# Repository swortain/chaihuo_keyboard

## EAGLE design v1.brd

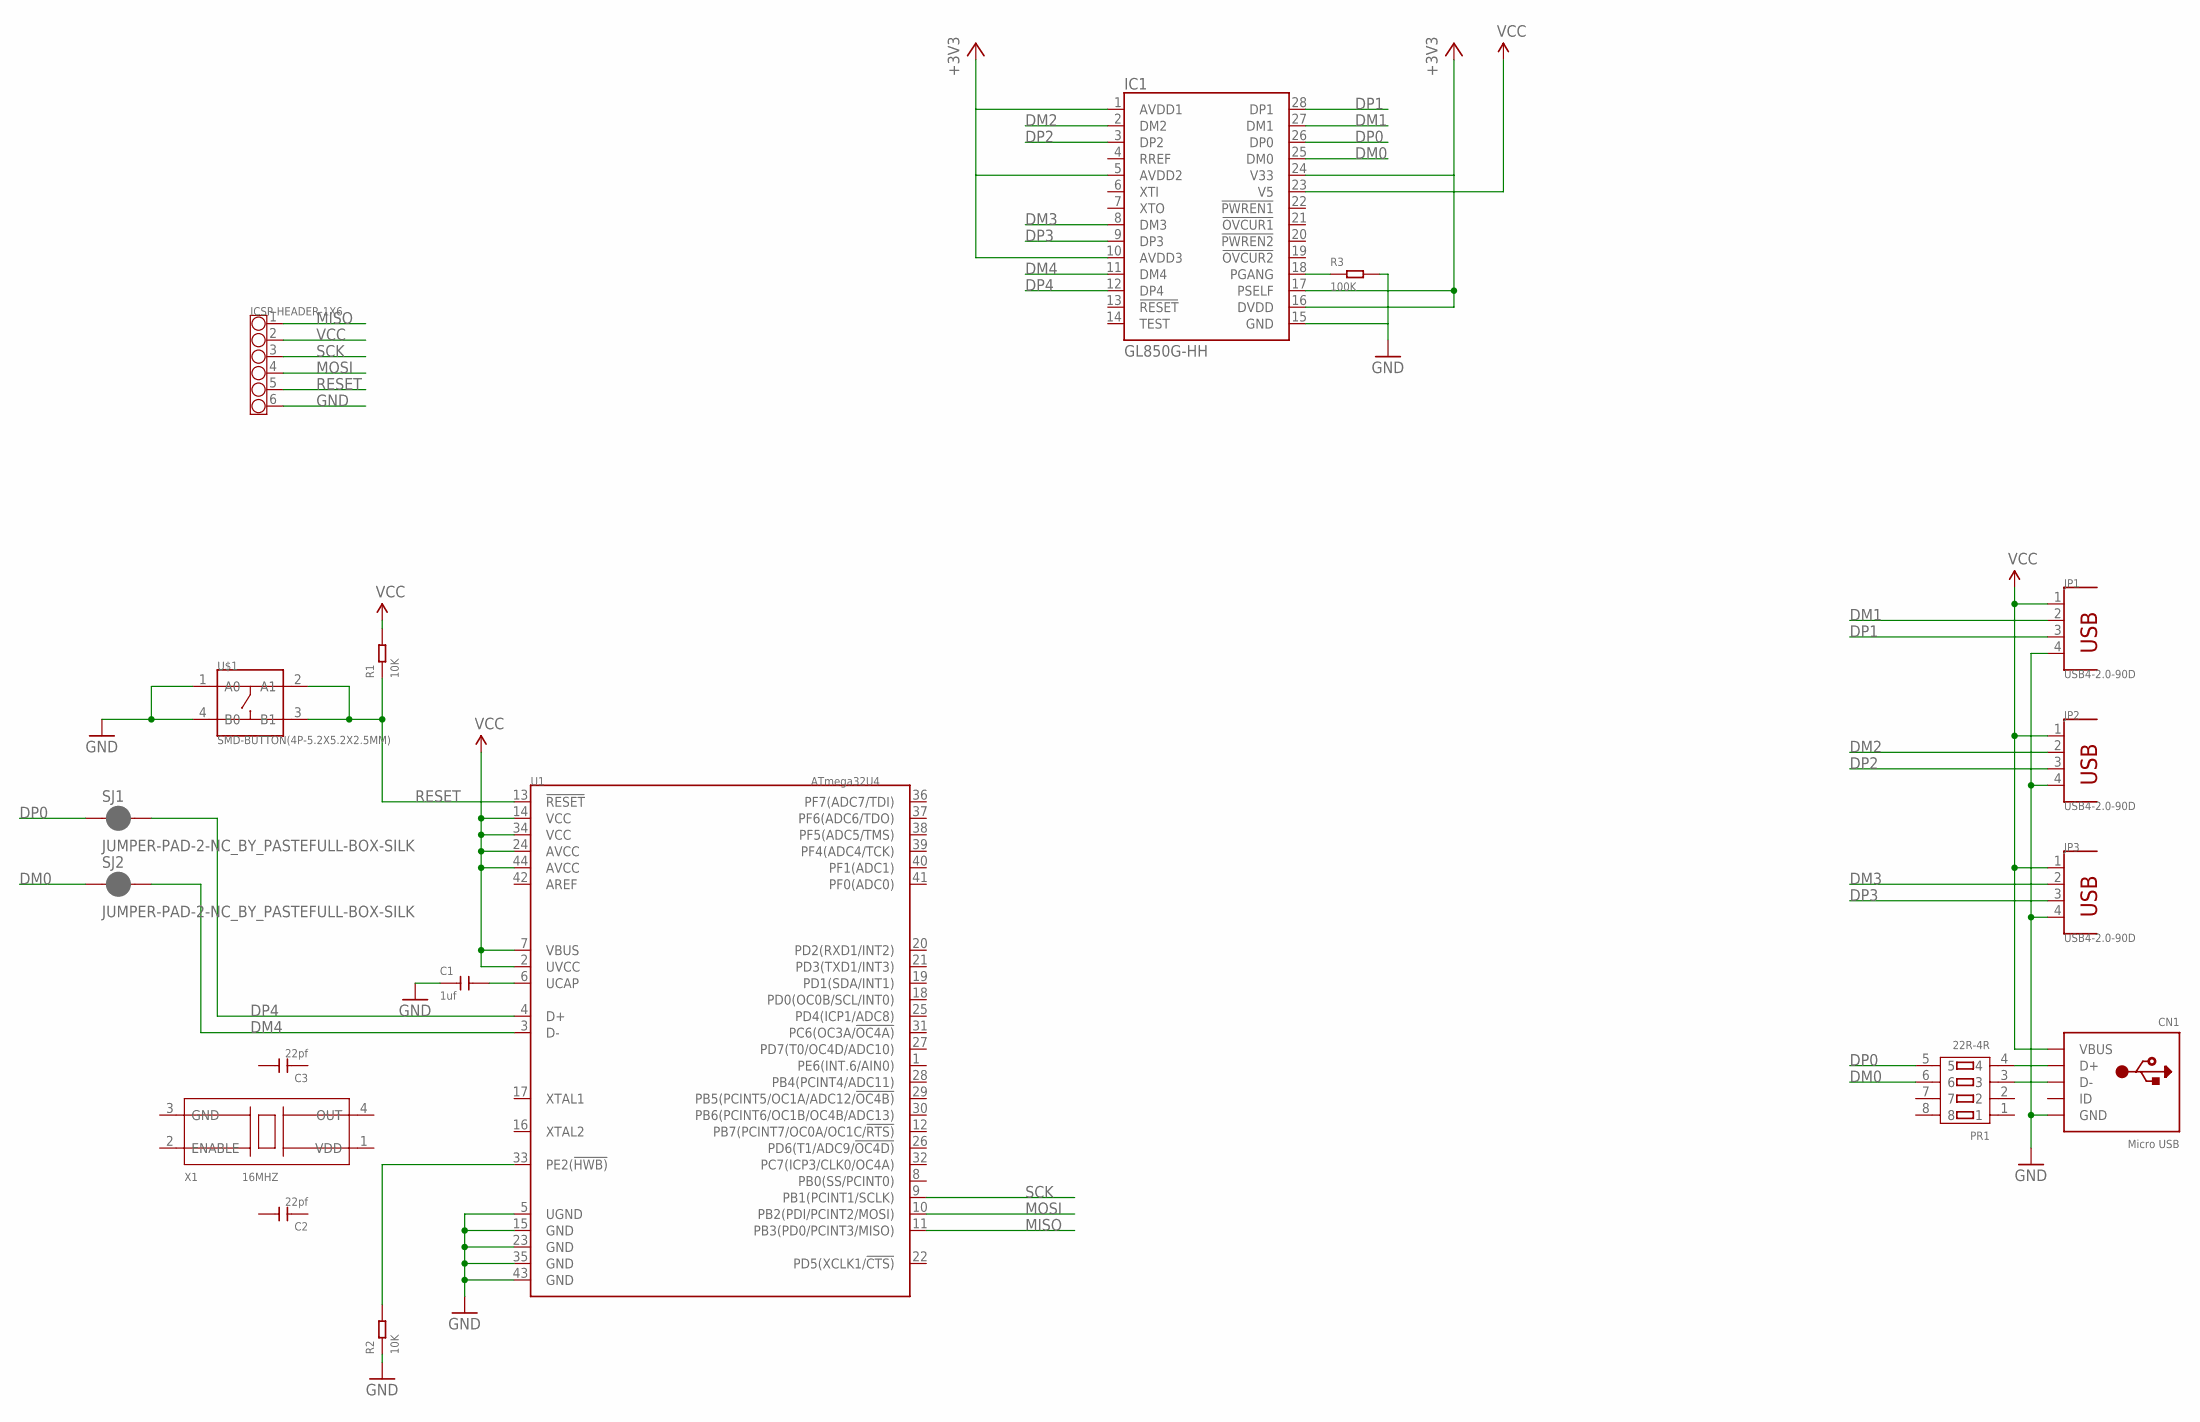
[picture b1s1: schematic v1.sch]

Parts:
C1: 1uf; C0603
C2, C3: 22pf; C0402
CN1: Micro USB; USB-MINIB
IC1: GL850G-HH; SSOP28
ICSP-HEADER-1X6: CONNECTOR-HEADER-6P-3460650P1; 1X6P-2.54-2.54-11.6-3.0-BLACK-MALE
JP1, JP2, JP3: USB4-2.0-90D; USB4+2P-2.0-90D
PR1: 22R-4R; RA1206-8
R1, R2: 10K; R0603
R3: 100K; R0805
SJ1, SJ2: JUMPER-PAD-2-NC_BY_PASTEFULL-BOX-SILK; PAD-JUMPER-2-NC_BY_PASTE_YES_SILK_FULL_BOX
U1: ATmega32U4; TQFP-44
U$1: SMD-BUTTON(4P-5.2X5.2X2.5MM); SW4-SMD-5.2X5.2X2.5MM
X1: 16MHZ; X4-SMD-3.2X2.5X0.7MM

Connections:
+3V3: IC1.1 (AVDD1), IC1.5 (AVDD2), IC1.10 (AVDD3), IC1.16 (DVDD), IC1.17 (PSELF), IC1.24 (V33)
DM0: IC1.25 (DM0), PR1.6, SJ2.1
DM1: IC1.27 (DM1), JP1.2
DM2: IC1.2 (DM2), JP2.2
DM3: IC1.8 (DM3), JP3.2
DM4: IC1.11 (DM4), SJ2.2, U1.3 (D-)
DP0: IC1.26 (DP0), PR1.5, SJ1.1
DP1: IC1.28 (DP1), JP1.3
DP2: IC1.3 (DP2), JP2.3
DP3: IC1.9 (DP3), JP3.3
DP4: IC1.12 (DP4), SJ1.2, U1.4 (D+)
GND: C1.1, CN1.GND, IC1.15 (GND), ICSP-HEADER-1X6.6, JP1.4, JP2.4, JP3.4, R2.1, R3.2, U1.5 (UGND), U1.15 (GND), U1.23 (GND), U1.35 (GND), U1.43 (GND), U$1.1 (A0), U$1.4 (B0)
MISO: ICSP-HEADER-1X6.1, U1.11 (PB3(PD0/PCINT3/MISO))
MOSI: ICSP-HEADER-1X6.4, U1.10 (PB2(PDI/PCINT2/MOSI))
unnamed: C1.2, U1.6 (UCAP)
unnamed: IC1.18 (PGANG), R3.1
unnamed: CN1.D+, PR1.4
unnamed: CN1.D-, PR1.3
unnamed: R2.2, U1.33 (PE2(!HWB))
RESET: ICSP-HEADER-1X6.5, R1.1, U1.13 (!RESET), U$1.2 (A1), U$1.3 (B1)
SCK: ICSP-HEADER-1X6.3, U1.9 (PB1(PCINT1/SCLK))
VCC: CN1.VBUS, IC1.23 (V5), ICSP-HEADER-1X6.2, JP1.1, JP2.1, JP3.1, R1.2, U1.2 (UVCC), U1.7 (VBUS), U1.14 (VCC), U1.24 (AVCC), U1.34 (VCC), U1.44 (AVCC)

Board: 2 copper layers, 18 parts (0 on the bottom side), 22 nets, no tracks yet.

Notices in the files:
parts and their libraries:
SparkFun-Passives: Licensing: Creative Commons ShareAlike 4.0 International - https://creativecommons.org/licenses/by-sa/4.0
